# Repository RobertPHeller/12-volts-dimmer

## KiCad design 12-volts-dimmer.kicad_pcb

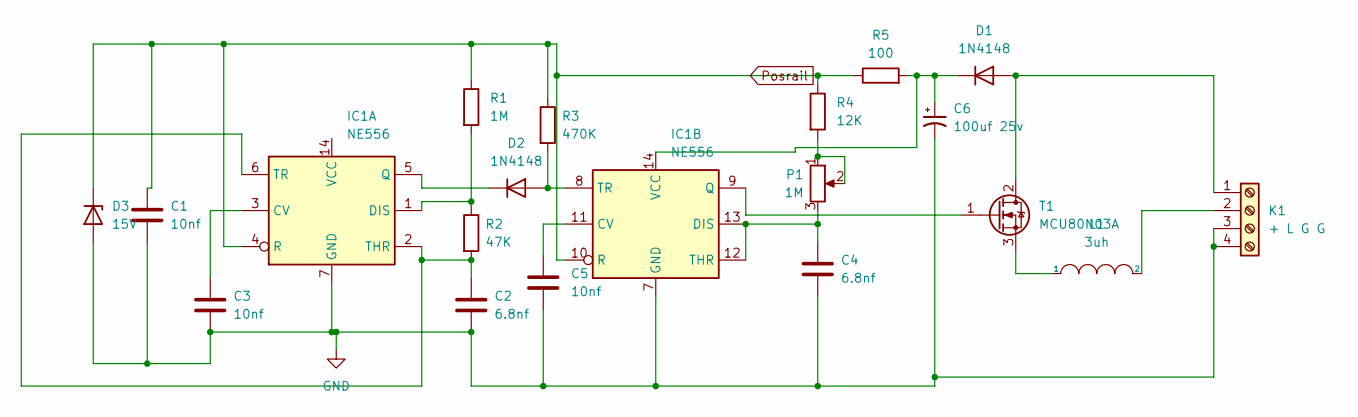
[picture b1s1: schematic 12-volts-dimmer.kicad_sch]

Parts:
C1, C3, C5: 10nf; C_0603_1608Metric; Mouser Part Number 80-C0603C103J5RAC
C2: 6.8nf; C_0603_1608Metric; Mouser Part Number 80-C0603C682K5R
C4: 6.8nf; C_0603_1608Metric; Mouser Part Number 80-C0603C103J5RAC
C6: 100uf 25v; CP_EIA-7343-31_Kemet-D; Mouser Part Number 80-T521D107M25AT7280
D1, D2: 1N4148; D_SOD-323; Mouser Part Number 833-1N4148WX-TP
D3: 15V; D_SOD-123; Mouser Part Number 833-MMSZ4702-TP
IC1: NE556
K1: + L G G; TerminalBlock_Phoenix_MKDS-1,5-4-5.08_1x04_P5.08mm_Horizont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; Mouser Part Number 651-1715747
L1: 3uh; L_Bourns-SRU1028_10.0x10.0mm; Mouser Part Number 652-SRU1048-3R0Y
P1: 1M; Potentiometer_Bourns_3314J_Vertical; Mouser Part Number 652-3314J-1-105E
R1: 1M; R_0603_1608Metric; Mouser Part Number 603-RC0603FR-071ML
R2: 47K; R_0603_1608Metric; Mouser Part Number 603-AC0603FR-1347KL
R3: 470K; R_0603_1608Metric; Mouser Part Number 603-RC0603FR-10470KL
R4: 12K; R_0603_1608Metric; Mouser Part Number 603-AC0603FR-0712KL
R5: 100; R_0805_2012Metric; Mouser Part Number 603-RC0805FR-07100RP
T1: MCU80N03A; TO-252-3_TabPin2; Mouser Part Number 833-MCU80N03A-TP

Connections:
GND: C1.2, C2.2, C3.2, C4.2, C5.2, C6.2, D3.2 (A), IC1.7 (GND), K1.3, K1.4
unnamed: C2.1, IC1.2 (THR), IC1.6 (TR), R2.2
unnamed: C3.1, IC1.3 (CV)
unnamed: C4.1, IC1.12 (THR), IC1.13 (DIS), P1.3
unnamed: C5.1, IC1.11 (CV)
unnamed: C6.1, D1.1 (K), IC1.14 (VCC), R5.2
unnamed: D1.2 (A), K1.1, T1.2 (D)
unnamed: D2.1 (K), IC1.5 (Q)
unnamed: D2.2 (A), IC1.8 (TR), R3.2
unnamed: K1.2, L1.2
unnamed: L1.1, T1.3 (S)
unnamed: IC1.1 (DIS), R1.2, R2.1
unnamed: P1.1, P1.2, R4.2
unnamed: IC1.9 (Q), T1.1 (G)
Posrail: C1.1, D3.1 (K), IC1.4 (R), IC1.10 (R), R1.1, R3.1, R4.1, R5.1

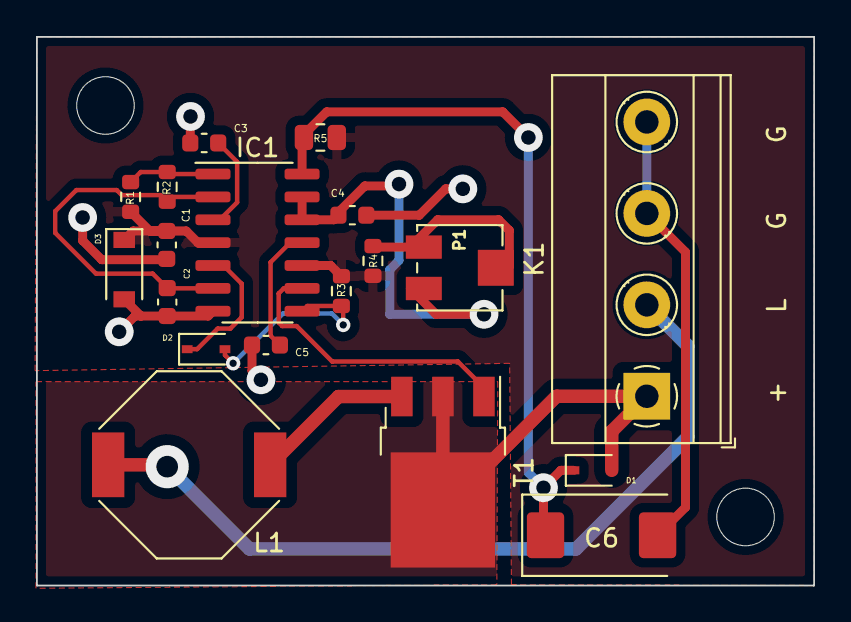
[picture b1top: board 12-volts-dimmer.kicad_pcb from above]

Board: 2 copper layers, 43.2 x 30.5 mm, 19 parts (0 on the bottom side), 15 nets.

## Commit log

2023-12-17 Init commit
2023-12-17 Minor updates.
2023-12-17 Clean up silk.
2023-12-17 Add dims, minor cosmetic updates.
